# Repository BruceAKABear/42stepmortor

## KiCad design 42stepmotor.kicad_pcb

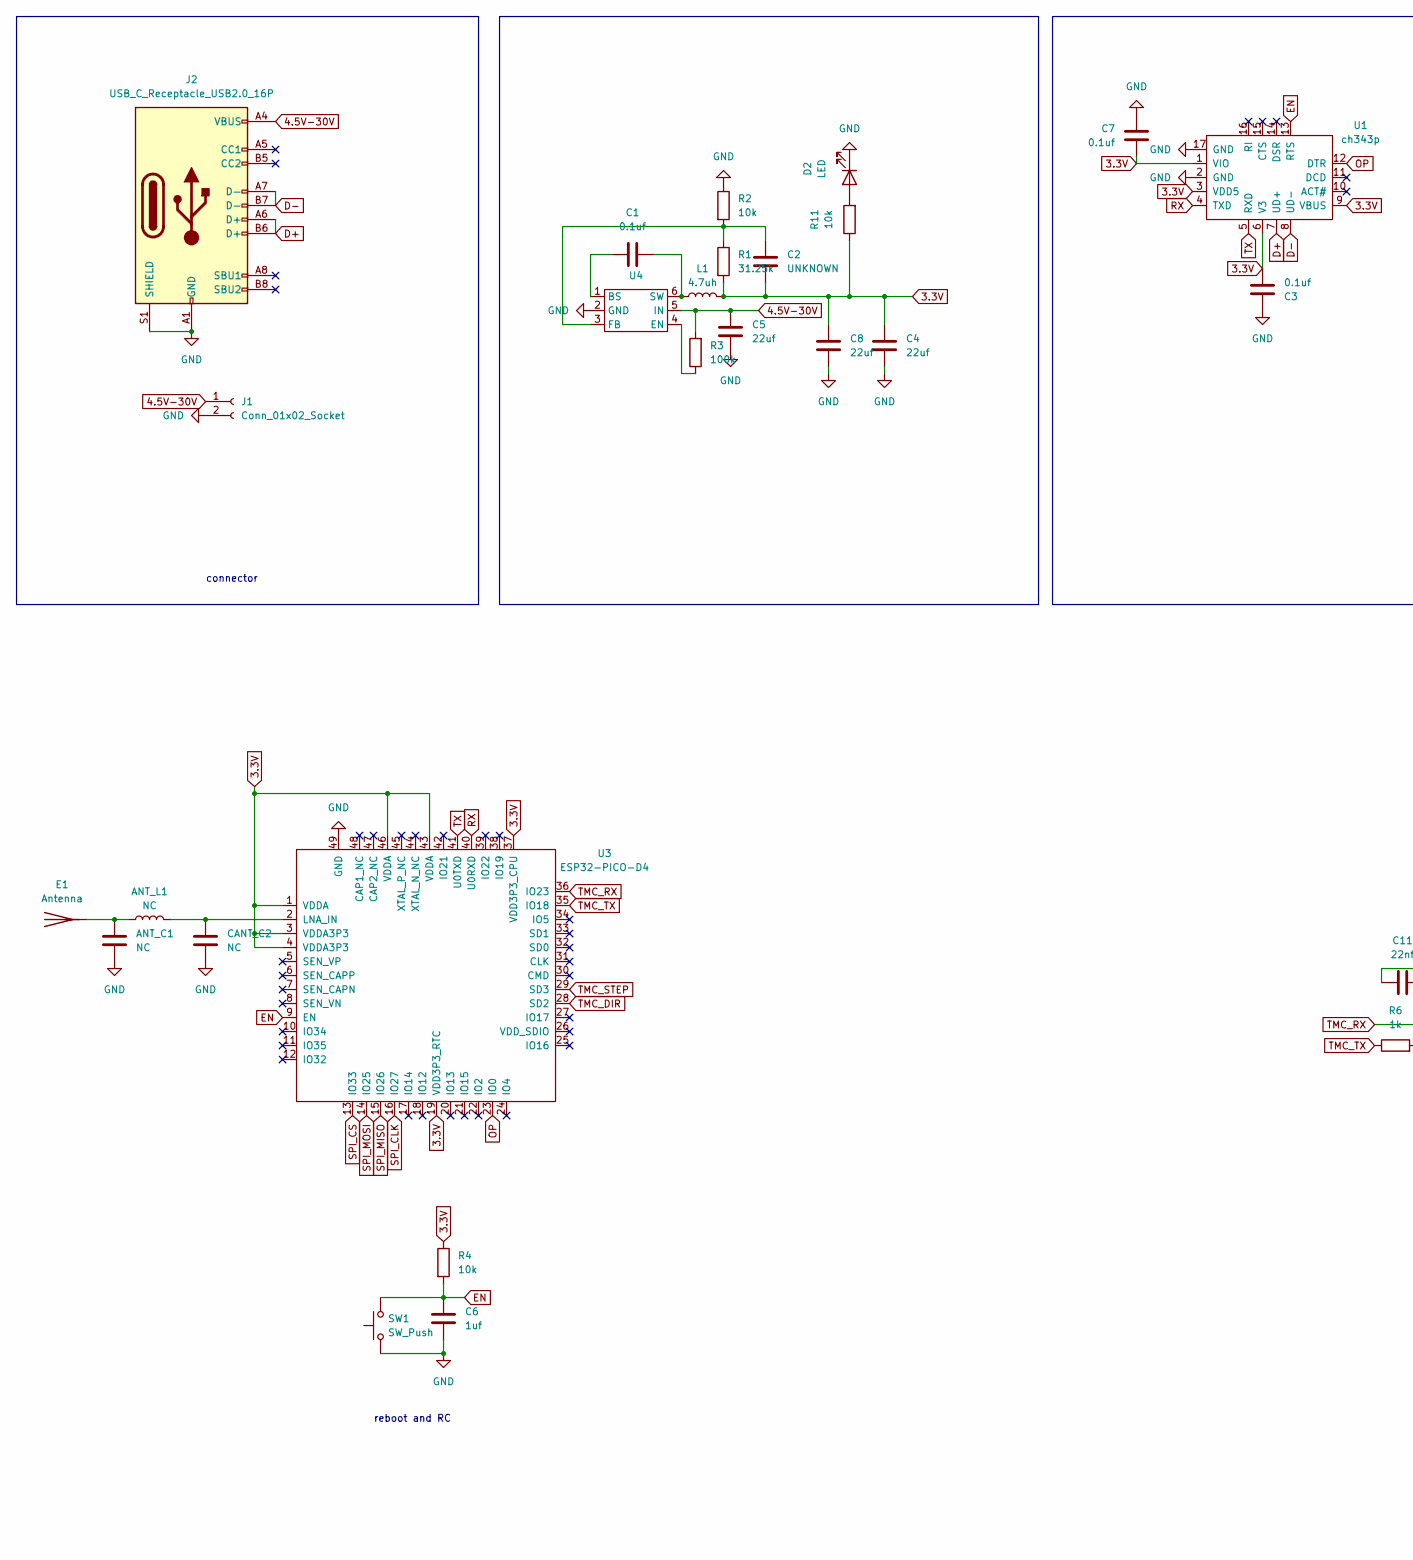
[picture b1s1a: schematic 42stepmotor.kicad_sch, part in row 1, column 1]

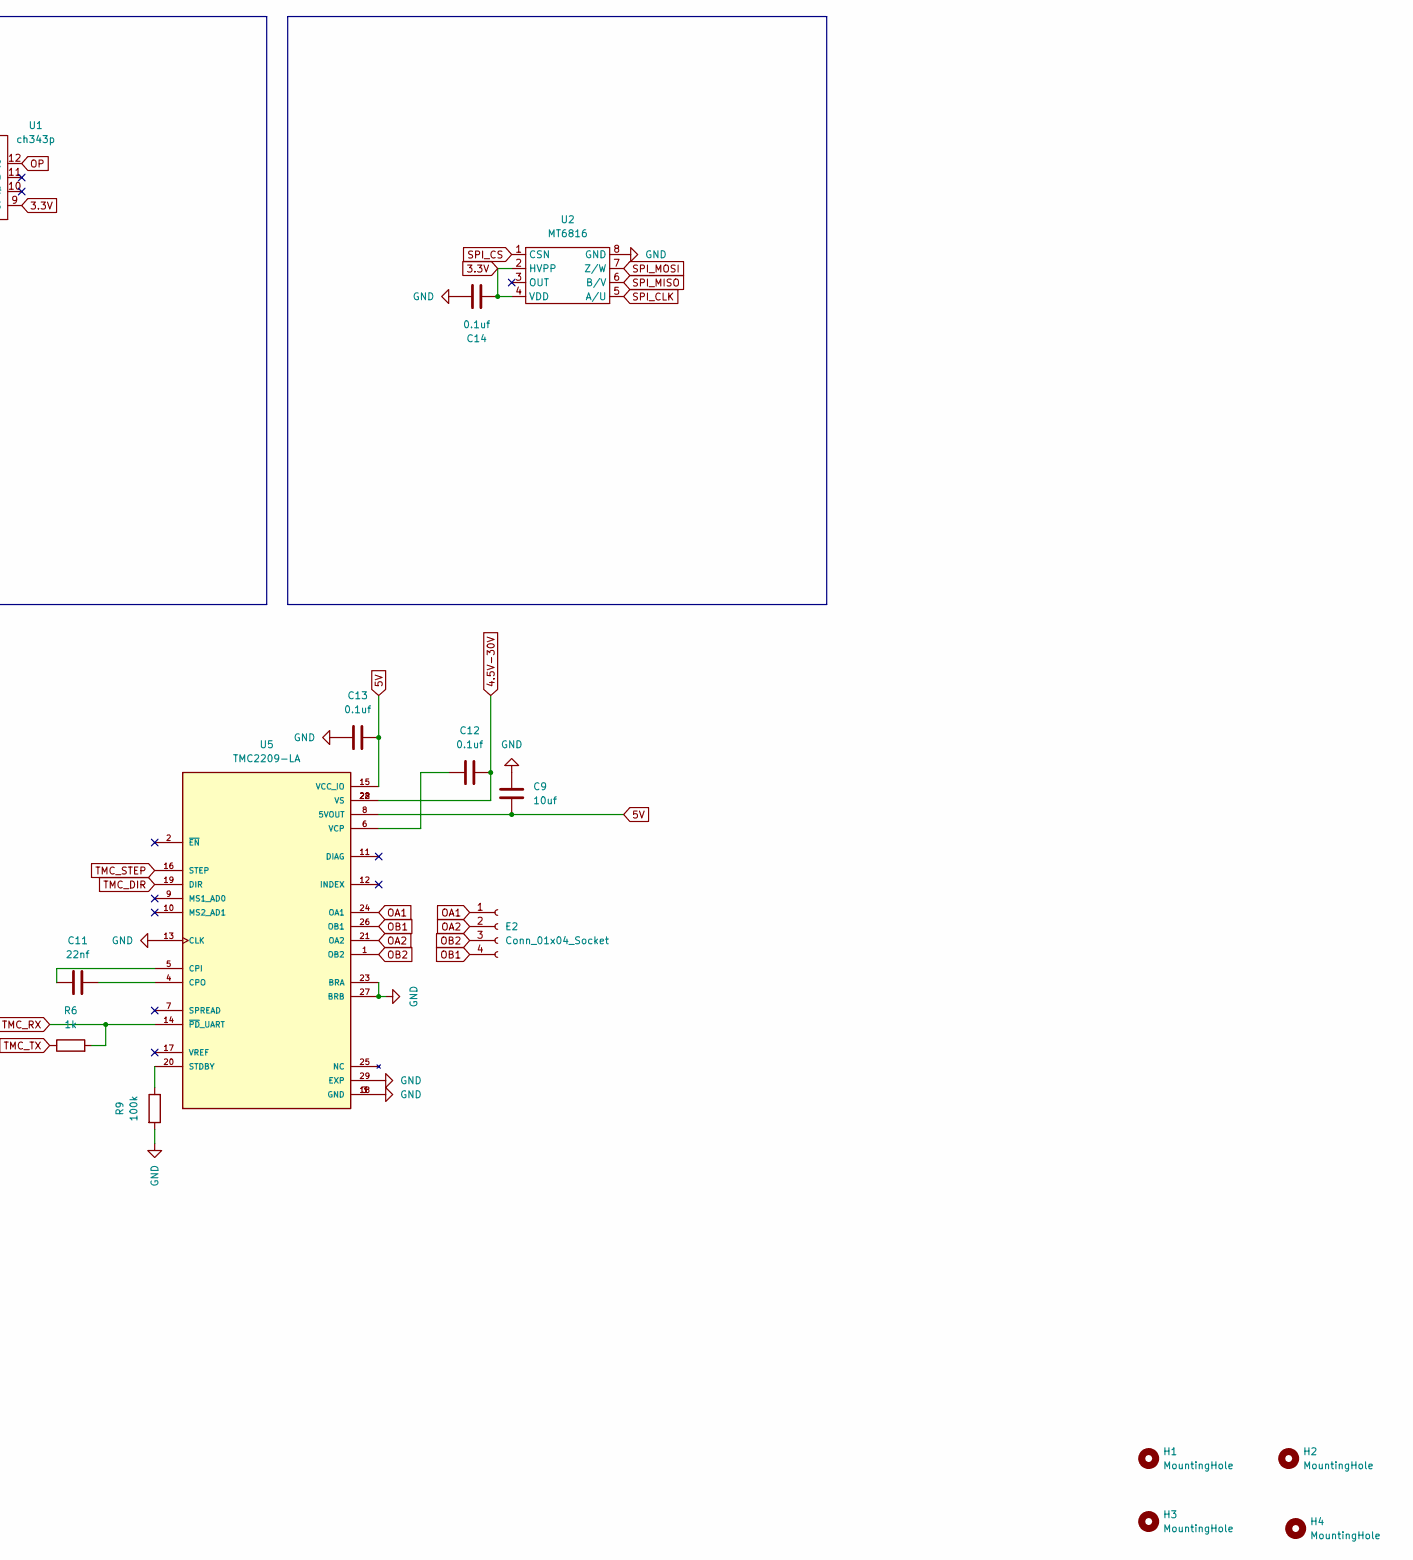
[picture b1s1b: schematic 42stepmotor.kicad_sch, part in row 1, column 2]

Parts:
ANT_C1: NC; C_0402_1005Metric
ANT_L1: NC; L_0402_1005Metric
C1, C12, C13, C14: 0.1uf; C_0603_1608Metric
C2: UNKNOWN; C_0603_1608Metric
C3, C7: 0.1uf; C_0402_1005Metric
C4, C5, C8: 22uf; C_0805_2012Metric
C6: 1uf; C_0402_1005Metric
C9: 10uf; C_0603_1608Metric
C11: 22nf; C_0603_1608Metric
CANT_C2: NC; C_0402_1005Metric
D2: LED; LED_0603_1608Metric
E1: Antenna; CA-03
E2: Conn_01x04_Socket; JST_XH_S4B-XH-A-1_1x04_P2.50mm_Horizontal
H1, H2, H3, H4: MountingHole; MountingHole_3.2mm_M3_Pad_Via
J1: Conn_01x02_Socket; JST_XH_S2B-XH-A-1_1x02_P2.50mm_Horizontal
J2: USB_C_Receptacle_USB2.0_16P; USB_C_Receptacle_HRO_TYPE-C-31-M-12
L1: 4.7uh; L_Cenker_CKCS4030
R1: 31.25k; R_0603_1608Metric
R2, R11: 10k; R_0603_1608Metric
R3, R9: 100k; R_0603_1608Metric
R4: 10k; R_0402_1005Metric
R6: 1k; R_0603_1608Metric
SW1: SW_Push; bt-342
U1: ch343p; QFN-16-1EP_3x3mm_P0.5mm_EP1.45x1.45mm
U2: MT6816; SO-8_3.9x4.9mm_P1.27mm
U3: ESP32-PICO-D4; QFN-48-1EP_7x7mm_P0.5mm_EP5.3x5.3mm
U4: SOT-23-6
U5: TMC2209-LA; QFN28_5X5_TRI; PARTREV 1.08

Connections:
3.3V: C2.2, C3.2, C4.1, C7.2, C8.1, C14.1, L1.2, R1.2, R4.1, R11.1, U1.1 (VIO), U1.3 (VDD5), U1.6 (V3), U1.9 (VBUS), U2.2 (HVPP), U2.4 (VDD), U3.1 (VDDA), U3.3 (VDDA3P3), U3.4 (VDDA3P3), U3.19 (VDD3P3_RTC), U3.37 (VDD3P3_CPU), U3.43 (VDDA), U3.46 (VDDA)
4.5V-30V: C5.1, C12.2, J1.1, J2.A4 (VBUS), J2.A9 (VBUS), J2.B4 (VBUS), J2.B9 (VBUS), R3.2, U4.5 (IN), U5.22 (VS), U5.28 (VS)
5V: C9.2, C13.2, U5.8 (5VOUT), U5.15 (VCC_IO)
D+: J2.A6 (D+), J2.B6 (D+), U1.7 (UD+)
D-: J2.A7 (D-), J2.B7 (D-), U1.8 (UD-)
EN: C6.1, R4.2, SW1.2, U1.13 (RTS), U3.9 (EN)
GND: ANT_C1.1, C3.1, C4.2, C5.2, C6.2, C7.1, C8.2, C9.1, C13.1, C14.2, CANT_C2.1, D2.1 (K), J1.2, J2.A1 (GND), J2.A12 (GND), J2.B1 (GND), J2.B12 (GND), J2.S1 (SHIELD), R2.1, R9.2, SW1.1, U1.2 (GND), U1.17 (GND), U2.8 (GND), U3.49 (GND), U4.2 (GND), U5.3 (GND), U5.13 (CLK), U5.18 (GND), U5.23 (BRA), U5.27 (BRB), U5.29 (EXP)
unnamed: D2.2 (A), R11.2
unnamed: ANT_C1.2, ANT_L1.1, E1.1 (A)
unnamed: ANT_L1.2, CANT_C2.2, U3.2 (LNA_IN)
unnamed: C1.2, U4.1 (BS)
unnamed: R3.1, U4.4 (EN)
unnamed: C2.1, R1.1, R2.2, U4.3 (FB)
unnamed: C1.1, L1.1, U4.6 (SW)
unnamed: C11.1, U5.5 (CPI)
unnamed: C11.2, U5.4 (CPO)
unnamed: R9.1, U5.20 (STDBY)
unnamed: C12.1, U5.6 (VCP)
OA1: E2.1, U5.24 (OA1)
OA2: E2.2, U5.21 (OA2)
OB1: E2.4, U5.26 (OB1)
OB2: E2.3, U5.1 (OB2)
OP: U1.12 (DTR), U3.23 (IO0)
RX: U1.4 (TXD), U3.40 (U0RXD)
SPI_CLK: U2.5 (A/U), U3.16 (IO27)
SPI_CS: U2.1 (CSN), U3.13 (IO33)
SPI_MISO: U2.6 (B/V), U3.15 (IO26)
SPI_MOSI: U2.7 (Z/W), U3.14 (IO25)
TMC_DIR: U3.28 (SD2), U5.19 (DIR)
TMC_RX: R6.2, U3.36 (IO23), U5.14 (~PD_UART)
TMC_STEP: U3.29 (SD3), U5.16 (STEP)
TMC_TX: R6.1, U3.35 (IO18)
TX: U1.5 (RXD), U3.41 (U0TXD)

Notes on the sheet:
reboot and RC
connector

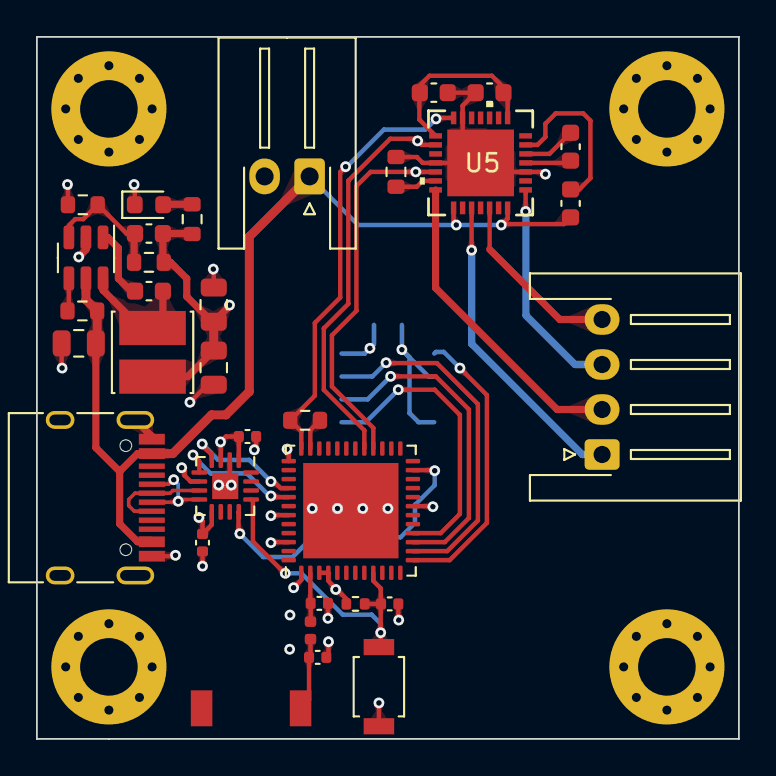
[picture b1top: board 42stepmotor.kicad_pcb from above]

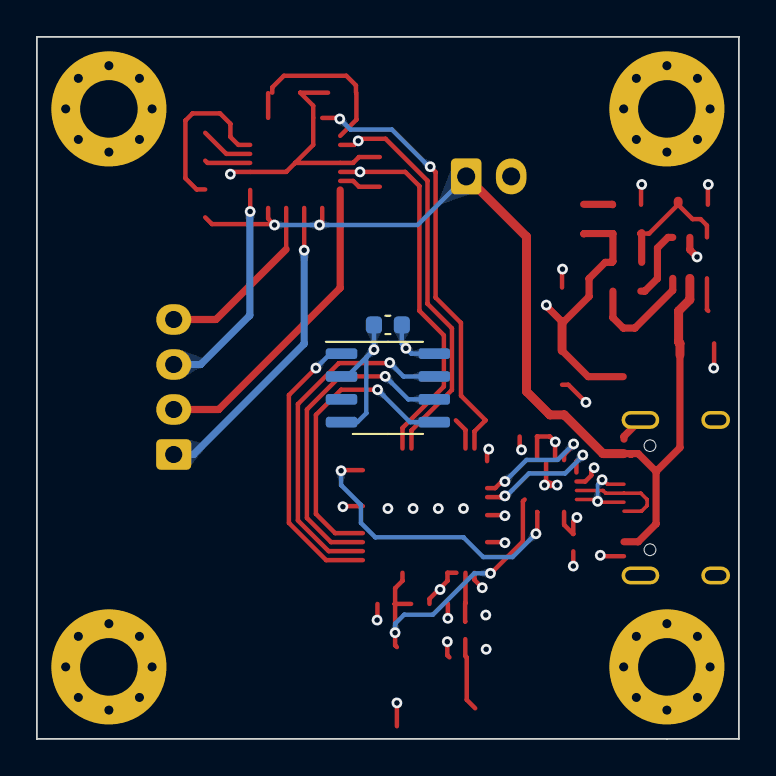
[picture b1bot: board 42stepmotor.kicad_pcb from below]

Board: 4 copper layers, 39.0 x 39.0 mm, 39 parts (2 on the bottom side), 33 nets.

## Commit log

2024-03-04 init
